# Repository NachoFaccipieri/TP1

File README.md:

**Segun chusmeamos a ojo con lolo tienen sentido los codigos y no deberia haber demasiado problema, pero para compilarlo/probarlo en el ciaa launcher necesitamos tener la placa conectada**

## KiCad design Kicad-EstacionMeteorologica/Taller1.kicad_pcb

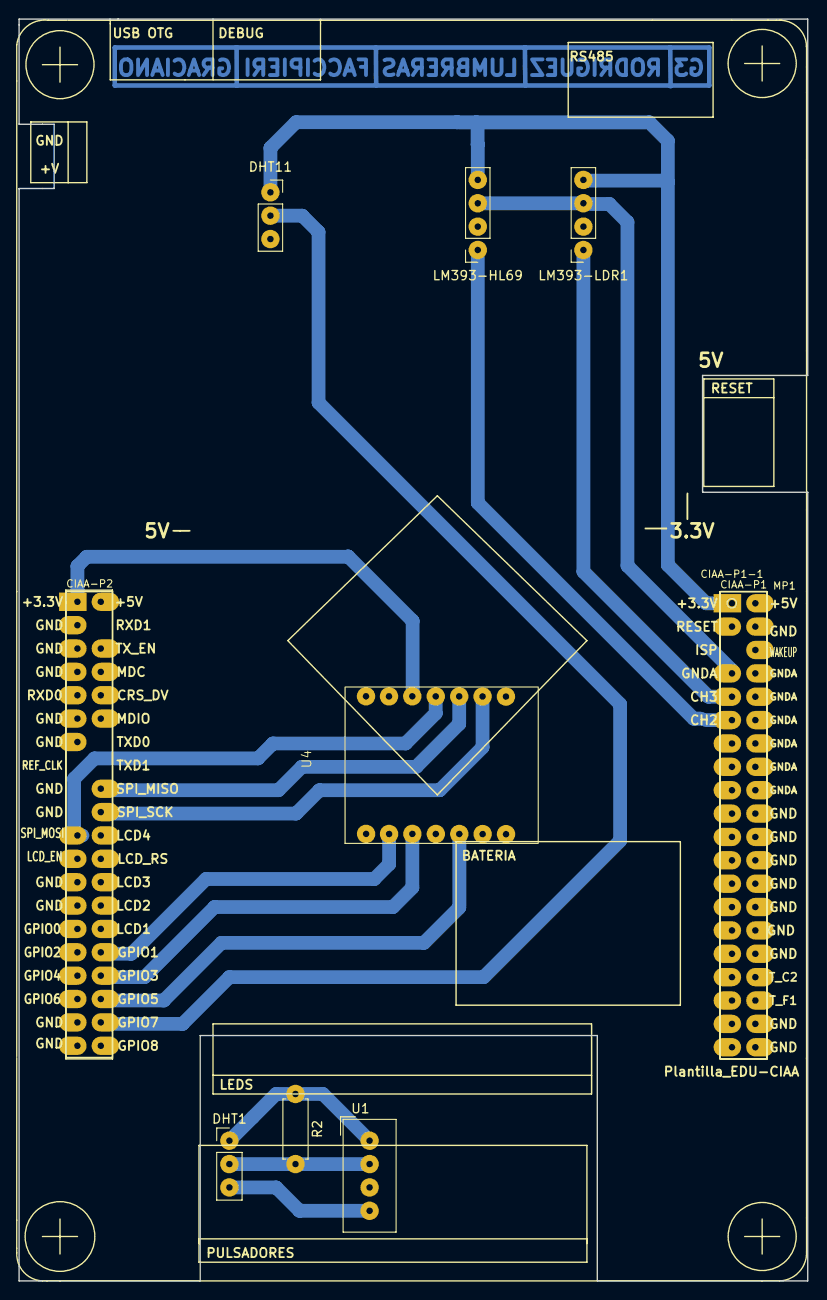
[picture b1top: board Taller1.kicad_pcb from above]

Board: 2 copper layers, 85.7 x 137.2 mm, 10 parts (0 on the bottom side), 14 nets.

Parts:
CIAA-P1-1: Conn_02x20_Odd_Even; P1Ciaa
CIAA-P2-1: Conn_02x20_Odd_Even; P2Ciaa
DHT1: Conn_01x03; PinHeader_1x03_P2.54mm_Vertical
DHT11: Conn_01x03; PinSocket_1x03_P2.54mm_Vertical
LM393-HL69, LM393-LDR1: Conn_01x04; PinSocket_1x04_P2.54mm_Vertical
MP1: Plantilla_EDU-CIAA
R2: 4700; R_Axial_DIN0207_L6.3mm_D2.5mm_P7.62mm_Horizontal
U1: DHT11; Aosong_DHT11_5.5x12.0_P2.54mm
U4: SX1262-XIAO; Untitled

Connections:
ADC2: CIAA-P1-1.11 (CH2), LM393-HL69.1
ADC3: CIAA-P1-1.9 (CH3), LM393-LDR1.1
Alimentacion 3.3v: CIAA-P1-1.1 (3V3), CIAA-P2-1.1 (3V3), DHT11.1, LM393-HL69.4, LM393-LDR1.4, U4.3 (3v3)
GND: CIAA-P2-1.3 (GND), CIAA-P2-1.5 (GND), CIAA-P2-1.7 (GND), CIAA-P2-1.11 (GND), CIAA-P2-1.13 (GND), CIAA-P2-1.25 (GND), CIAA-P2-1.27 (GND), CIAA-P2-1.37 (GND), CIAA-P2-1.39 (GND), DHT11.3, U4.2 (GND)
GNDA: CIAA-P1-1.7 (GNDA), LM393-HL69.3, LM393-LDR1.3
GPIO1: CIAA-P2-1.32 (GPIO1), U4.9 (DIO1)
GPIO3: CIAA-P2-1.34 (GPIO3), U4.10 (RST)
GPIO5: CIAA-P2-1.36 (GPIO5), U4.12 (NSS)
GPIO7: CIAA-P2-1.38 (GPIO7), DHT11.2
unnamed: DHT1.2, R2.2, U1.2 (DATA)
unnamed: DHT1.1, R2.1, U1.1 (VDD)
SPI/MISO: CIAA-P2-1.18 (SPI_MISO), U4.5 (MISO)
SPI/MOSI: CIAA-P2-1.21 (SPI_MOSI), U4.4 (MOSI)
SPI/SCK: CIAA-P2-1.20 (SPI_SCK), U4.6 (SCK)

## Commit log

2025-09-15 modificaciones dashboard
2025-09-18 movi archivos
2025-09-26 4 cards
2025-09-26 cards
2025-09-27 cambios del kicad q hizo lolo
2025-10-13 Código sensor de luz funcionando.
2025-10-13 codigo humedad suelo
    falta probarlo.
2025-10-16 Programa main actualizado
    Crear en el embedded IDE el new program y pegar estos programas.
2025-10-16 Programa principal actualizado
    Para ejecutarlo crear un new program y pegar estos programas.
2025-10-22 Avances con Lora
2025-10-22 Subo Kicadd Actualizado
2025-10-23 Ultima versao de KiCad
2025-10-30 Codigos para copilot
2025-10-30 chats agregados
2025-10-31 ultima version PCB
2025-11-03 mas codigo
2025-11-03 codigo de dht11
2025-11-03 Kicad terminado
2025-11-08 reorganizando ando
2025-11-18 Ultima version pistas curvas
    cambios de lolo.
2025-11-18 Ultima version pistas pulidas
    Ultima version de lolo.
2025-11-18 Ultima version pistas pulidas
    Cambios de lolo.
2025-11-18 IMPRIMIR
2025-12-10 empezando de 0
2025-12-11 Intentos
2026-01-15 Rak y ESP32 andan
2026-01-18 Educia + lora32 + RAK
2026-01-24 Ordenando
2026-01-26 Funcionando
2026-01-29 En program_main y cod.BajoCons.LORA estan los codes
2026-01-29 Add initial README content about code usage
2026-02-02 Falta_BajoConsumo
2026-02-08 Terminado
